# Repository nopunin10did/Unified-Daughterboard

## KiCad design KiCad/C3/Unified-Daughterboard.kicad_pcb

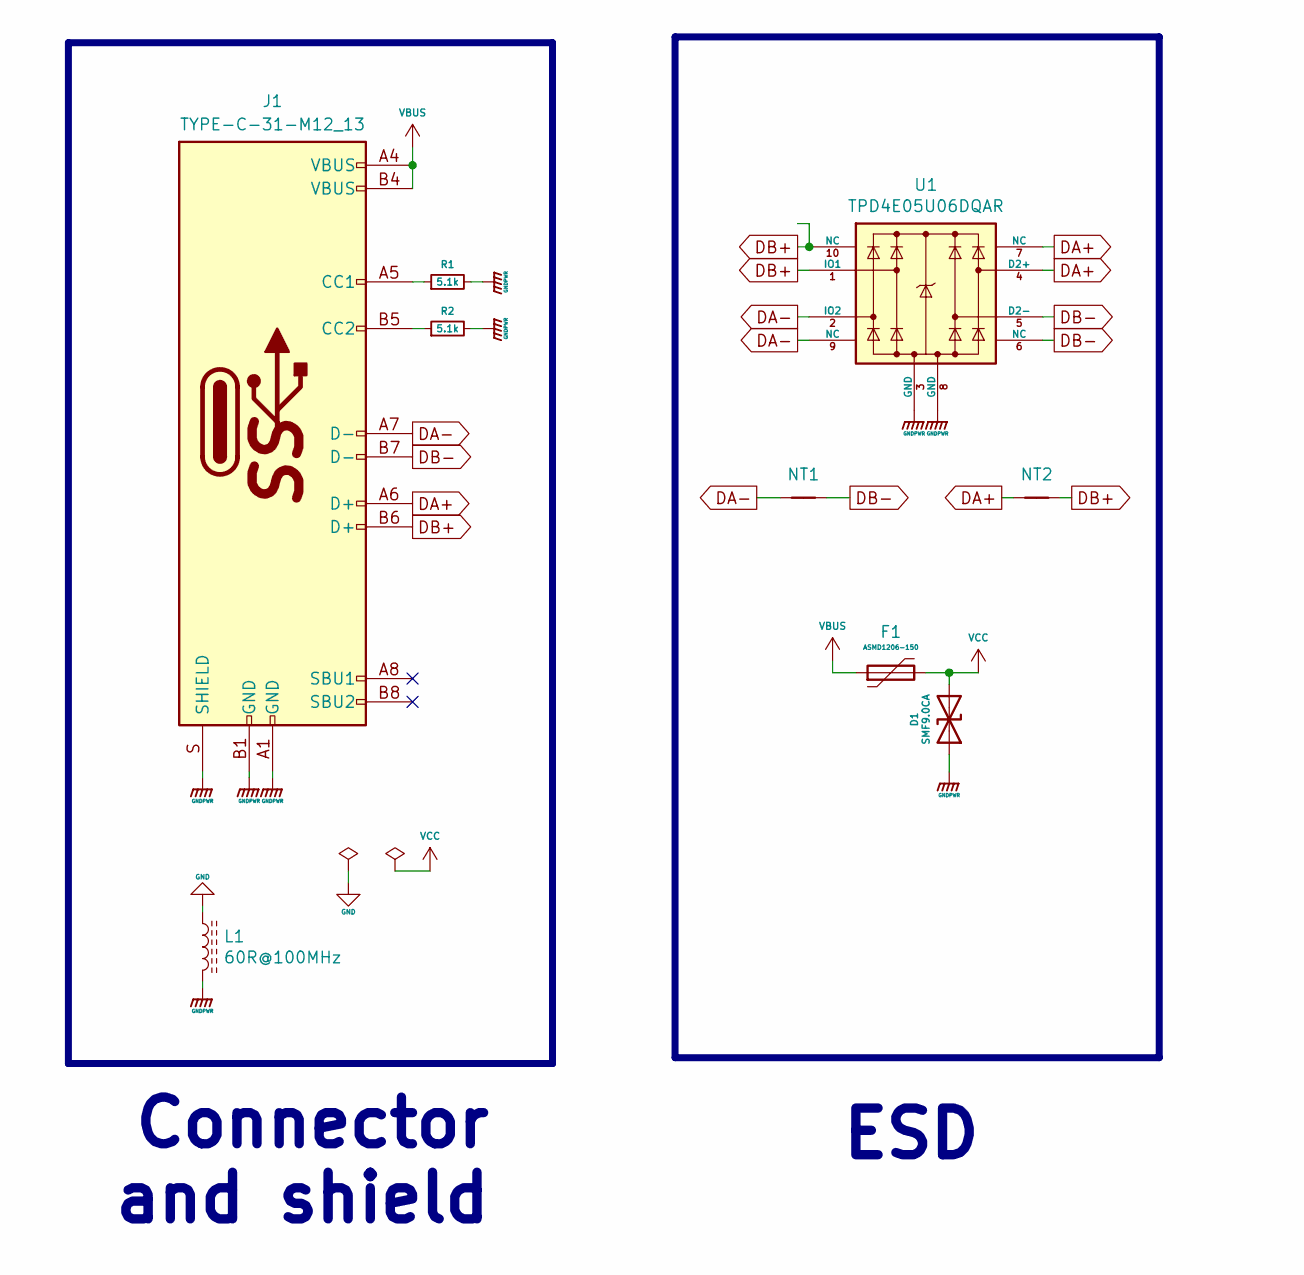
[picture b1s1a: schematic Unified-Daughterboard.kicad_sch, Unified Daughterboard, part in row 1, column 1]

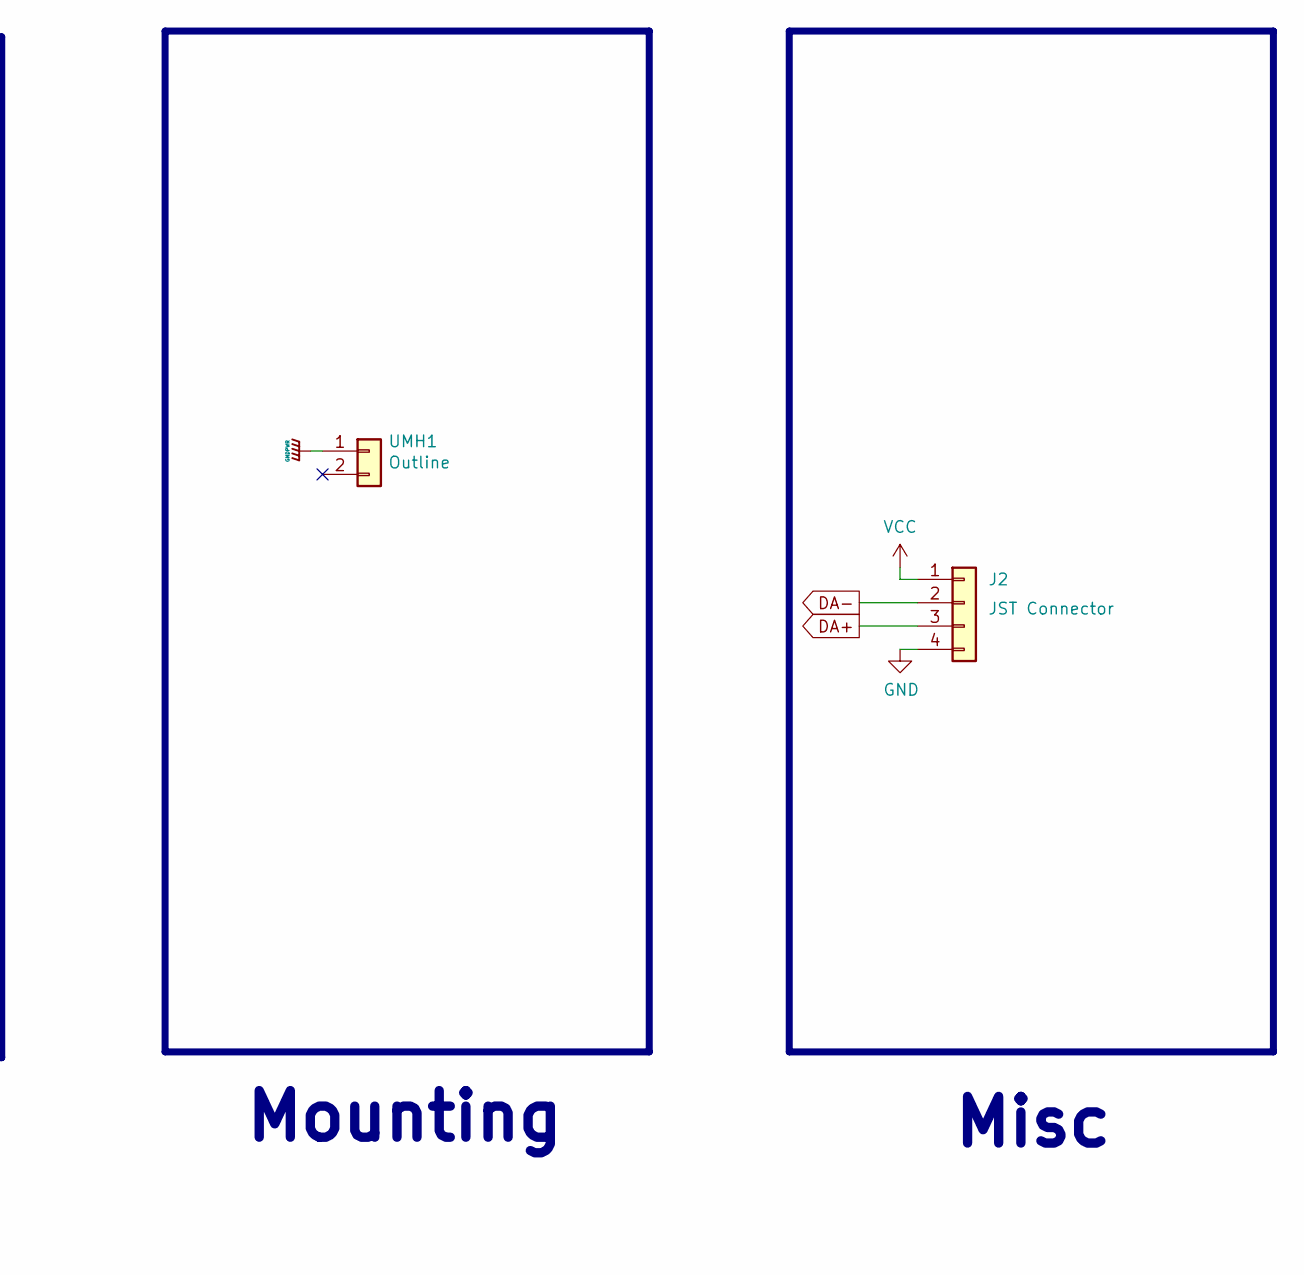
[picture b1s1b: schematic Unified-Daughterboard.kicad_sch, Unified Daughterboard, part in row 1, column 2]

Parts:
D1: SMF9.0CA; D_SOD-123_Bidirectional; Manufacturer Part No SMF9.0CA; LCSC Part No C123799
F1: ASMD1206-150; Fuse_1206_3216Metric; Manufacturer Part No ASMD1206-150; LCSC Part No C135342
J1: TYPE-C-31-M12_13; TYPE-C-31-M-12; Manufacturer Part No TYPE-C-31-M-12; LCSC Part No C165948
J2: JST Connector; Jushuo-AFC10-SO4QCC-00-4x1-SMD-connector; Manufacturer Part No SM04B-SRSS-TB(LF)(SN); LCSC Part No C160404
L1: 60R@100MHz; L_1206_3216Metric; Manufacturer Part No MLB3216-600P4A(f); LCSC Part No C33600
NT1, NT2: NetTie_2; NetTie-2_SMD_Tiny
R1, R2: 5.1k; R_0603
U1: TPD4E05U06DQAR; USON-10_2.5x1.0mm_P0.5mm; Manufacturer Part No TPD4E05U06DQAR; LCSC Part No C138714
UMH1: Outline; leopold_db_trimmer

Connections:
DA+: J1.A6 (D+), J2.3, NT2.1, U1.4 (D2+), U1.7 (NC)
DA-: J1.A7 (D-), J2.2, NT1.1, U1.2 (IO2), U1.9 (NC)
DB+: J1.B6 (D+), NT2.2, U1.1 (IO1), U1.10 (NC)
DB-: J1.B7 (D-), NT1.2, U1.5 (D2-), U1.6 (NC)
GND: J2.4, L1.1
GNDPWR: D1.1 (A1), J1.A1 (GND), J1.B1 (GND), J1.S (SHIELD), L1.2, R1.2, R2.2, U1.3 (GND), U1.8 (GND), UMH1.1
unnamed: J1.A5 (CC1), R1.1
unnamed: J1.B5 (CC2), R2.1
VBUS: F1.1, J1.A4 (VBUS), J1.B4 (VBUS)
VCC: D1.2 (A2), F1.2, J2.1

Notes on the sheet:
Misc
ESD
Mounting
Connector and shield

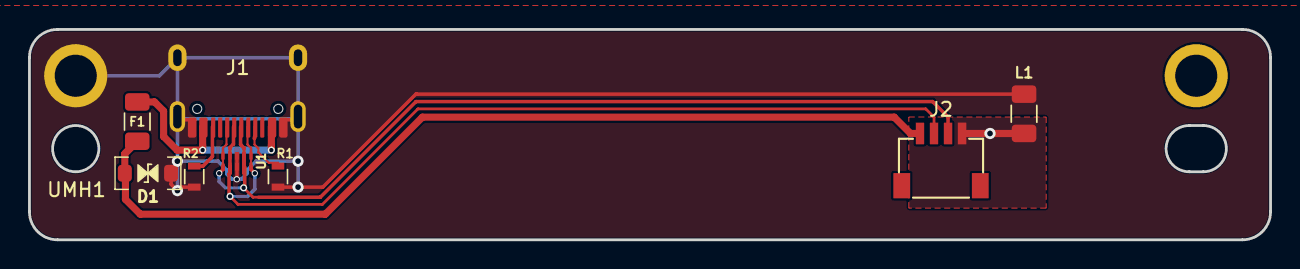
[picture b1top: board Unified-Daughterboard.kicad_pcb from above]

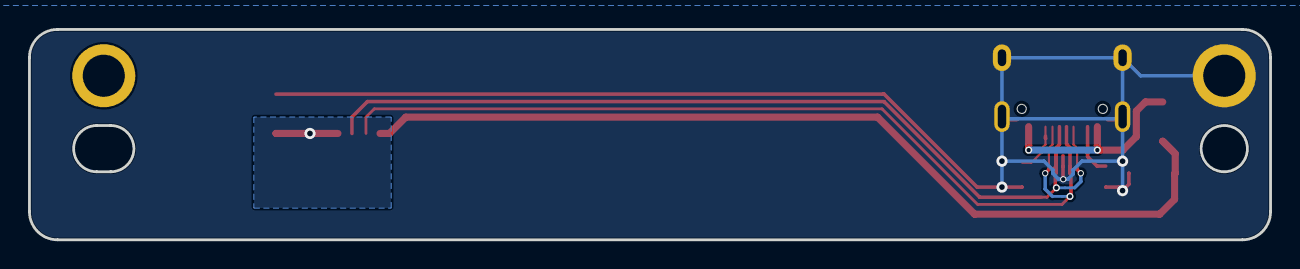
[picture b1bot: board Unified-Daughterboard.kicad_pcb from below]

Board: 2 copper layers, 88.5 x 15.0 mm, 11 parts (2 on the bottom side), 10 nets.

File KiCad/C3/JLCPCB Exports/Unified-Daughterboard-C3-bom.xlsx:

Comment | Designator | Footprint | LCSC Part Number
SMF9.0CA | D1 | SOD-123F | C123799
ASMD1206-150 | F1 | 1206 | C135342
SM04B-SRSS-TB(LF)(SN) | J2 | JST-SR-4 | C160404
TYPE-C-31-M12_13 | J1 | SMD | C165948
60R@100MHz | L1 | 1206 | C33600
5.1k | R1,R2 | 0603 | C23186
TPD4E05U06DQAR | U1 | uSON-10 | C138714

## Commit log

2022-10-31 Make version with JLCPCB tooling holes and ID number
2022-11-16 660 daughterboard outline and rearrangement
2022-11-17 Trimmer version
